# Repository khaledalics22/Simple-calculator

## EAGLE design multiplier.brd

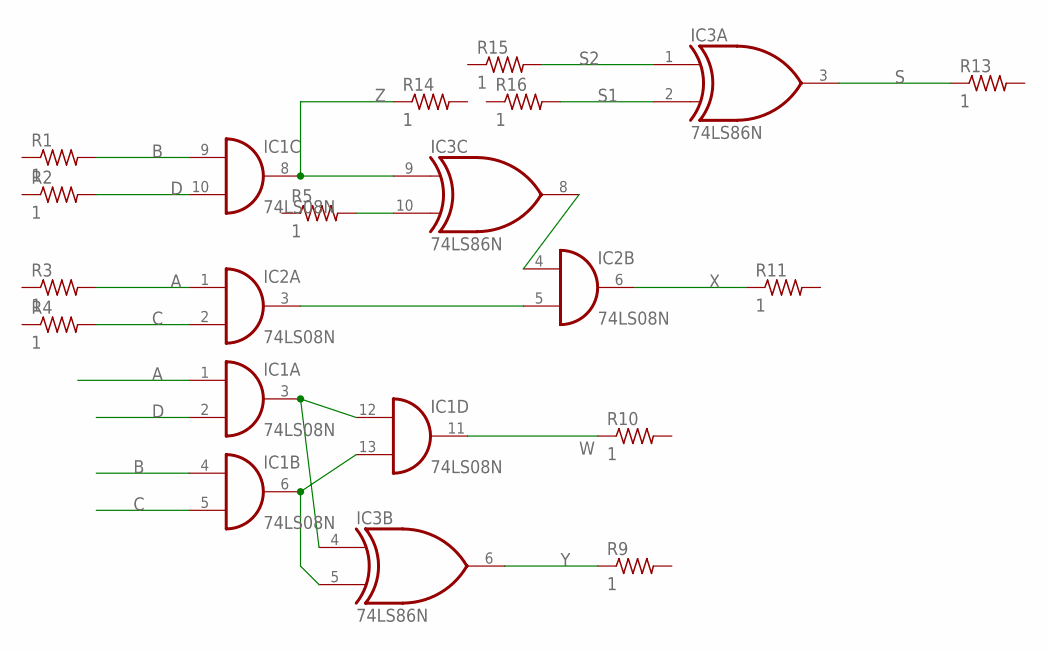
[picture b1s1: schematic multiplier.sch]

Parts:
IC1, IC2: 74LS08N; DIL14
IC3: 74LS86N; DIL14
R1, R2, R3, R4, R5, R9, R10, R11, R13, R14, R15, R16: 1; 0204V

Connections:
A: IC1.1 (I0), IC2.1 (I0), R3.2
B: IC1.4 (I0), IC1.9 (I0), R1.2
C: IC1.5 (I1), IC2.2 (I1), R4.2
D: IC1.2 (I1), IC1.10 (I1), R2.2
GND: IC1.7 (GND), IC2.7 (GND), IC3.7 (GND)
unnamed: IC1.3 (O), IC1.12 (I0), IC3.4 (I0)
unnamed: IC1.6 (O), IC1.13 (I1), IC3.5 (I1)
unnamed: IC3.10 (I1), R5.2
unnamed: IC2.3 (O), IC2.5 (I1)
S: IC3.3 (O), R13.1
S1: IC3.2 (I1), R16.2
S2: IC3.1 (I0), R15.2
VCC: IC1.14 (VCC), IC2.14 (VCC), IC3.14 (VCC)
W: IC1.11 (O), R10.1
X: IC2.6 (O), R11.1
Y: IC3.6 (O), R9.1
Z: IC1.8 (O), IC3.9 (I0), R14.1

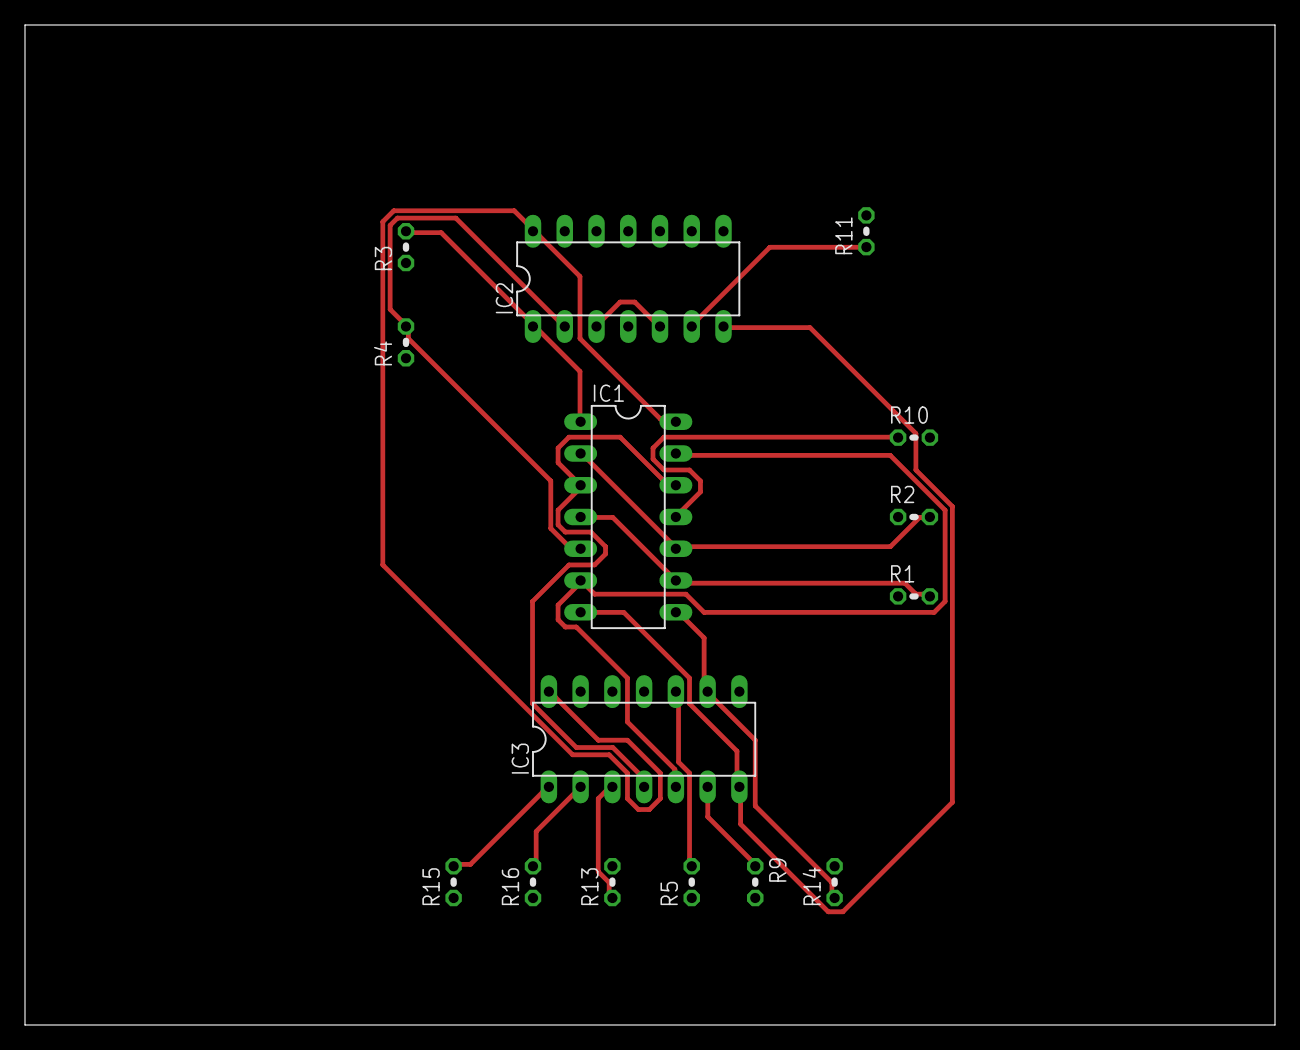
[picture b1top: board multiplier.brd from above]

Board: 2 copper layers, 100.0 x 80.0 mm, 15 parts (0 on the bottom side), 17 nets.
